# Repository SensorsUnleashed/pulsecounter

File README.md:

# Pulse Counter board

Simple mains powered board that will count any pulses applied to the connector.

RJ45 Connector Pin-out:
* RJ45 Pin 2 - VCC
* RJ45 Pin 5 - GND
* RJ45 Pin 6 - TTL Data

An example of a sensor that will fit the connector directly, can be found here: [Optical Utility Meter LED Pulse Sensor](https://openenergymonitor.org/emon/opticalpulsesensor)

Below you can see the prototype board.

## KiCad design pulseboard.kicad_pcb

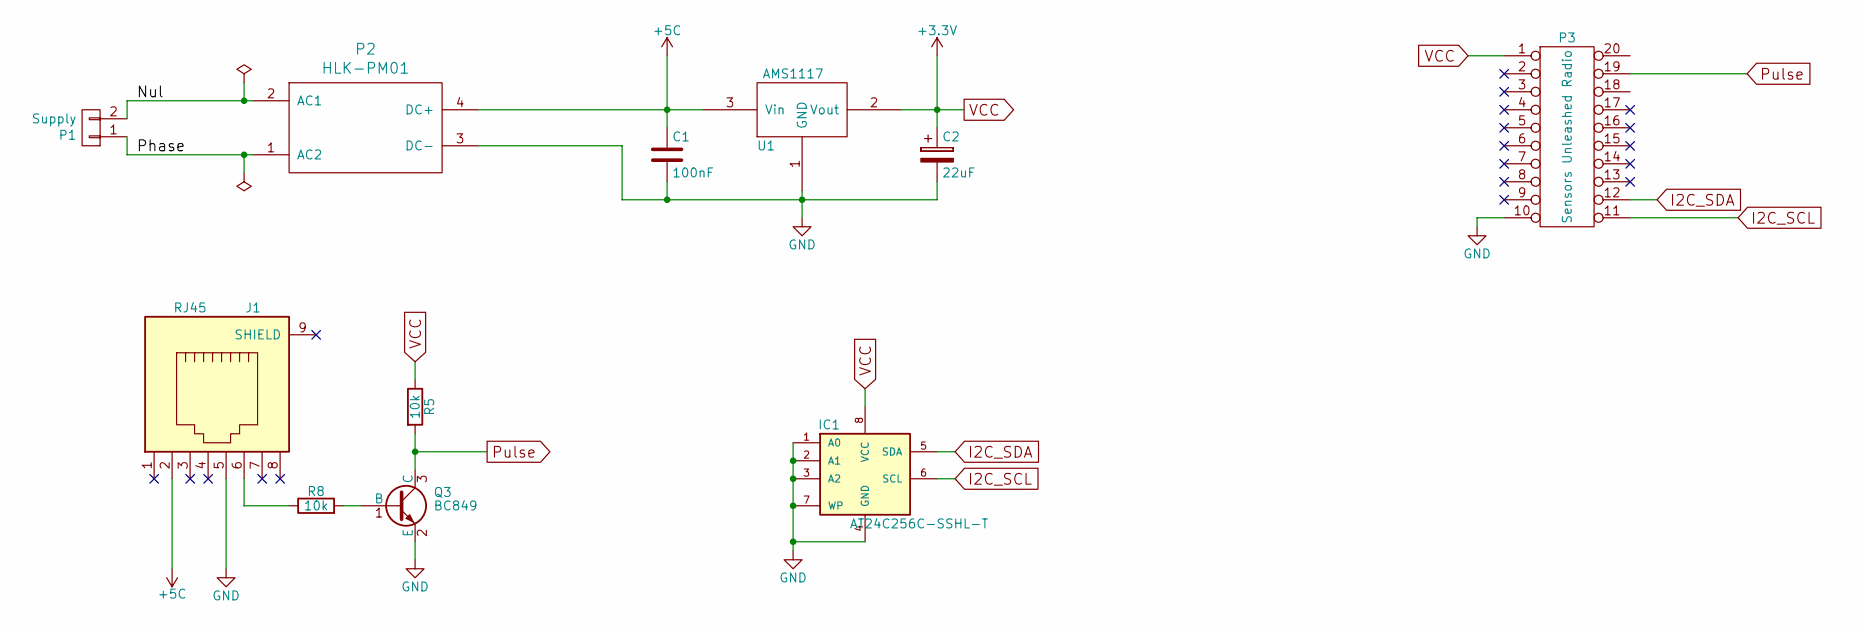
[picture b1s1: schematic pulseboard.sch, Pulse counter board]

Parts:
C1: 100nF; C_0805; Manufacturer Part Number 08053C104KAT2A
C2: 22uF; C_0805; Manufacturer Part Number F981A226MSA
IC1: AT24C256C-SSHL-T; SOIC-8_3.9x4.9mm_Pitch1.27mm
J1: RJ45; RJ45_8
P1: Supply; AK300-2
P2: HLK-PM01
P3: Sensors Unleashed Radio; zb3219PA_radio
Q3: BC849; SOT-23; Manufacturer Part Number BC849C-TP
R5, R8: 10k; R_0805
U1: AMS1117; SOT-223; Manufacturer Part Number AMS1117-3.3

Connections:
+5C: C1.1, J1.2, P2.4 (DC+), U1.3 (Vin)
/Nul: P1.2, P2.2 (AC1)
/Phase: P1.1, P2.1 (AC2)
GND: C1.2, C2.2, IC1.1 (A0), IC1.2 (A1), IC1.3 (A2), IC1.4 (GND), IC1.7 (WP), J1.5, P2.3 (DC-), P3.10, Q3.2 (E), U1.1 (GND)
I2C_SCL: IC1.6 (SCL), P3.11
I2C_SDA: IC1.5 (SDA), P3.12
unnamed: J1.6, R8.1
unnamed: Q3.1 (B), R8.2
Pulse: P3.19, Q3.3 (C), R5.2
VCC: C2.1, IC1.8 (VCC), P3.1, R5.1, U1.2 (Vout)

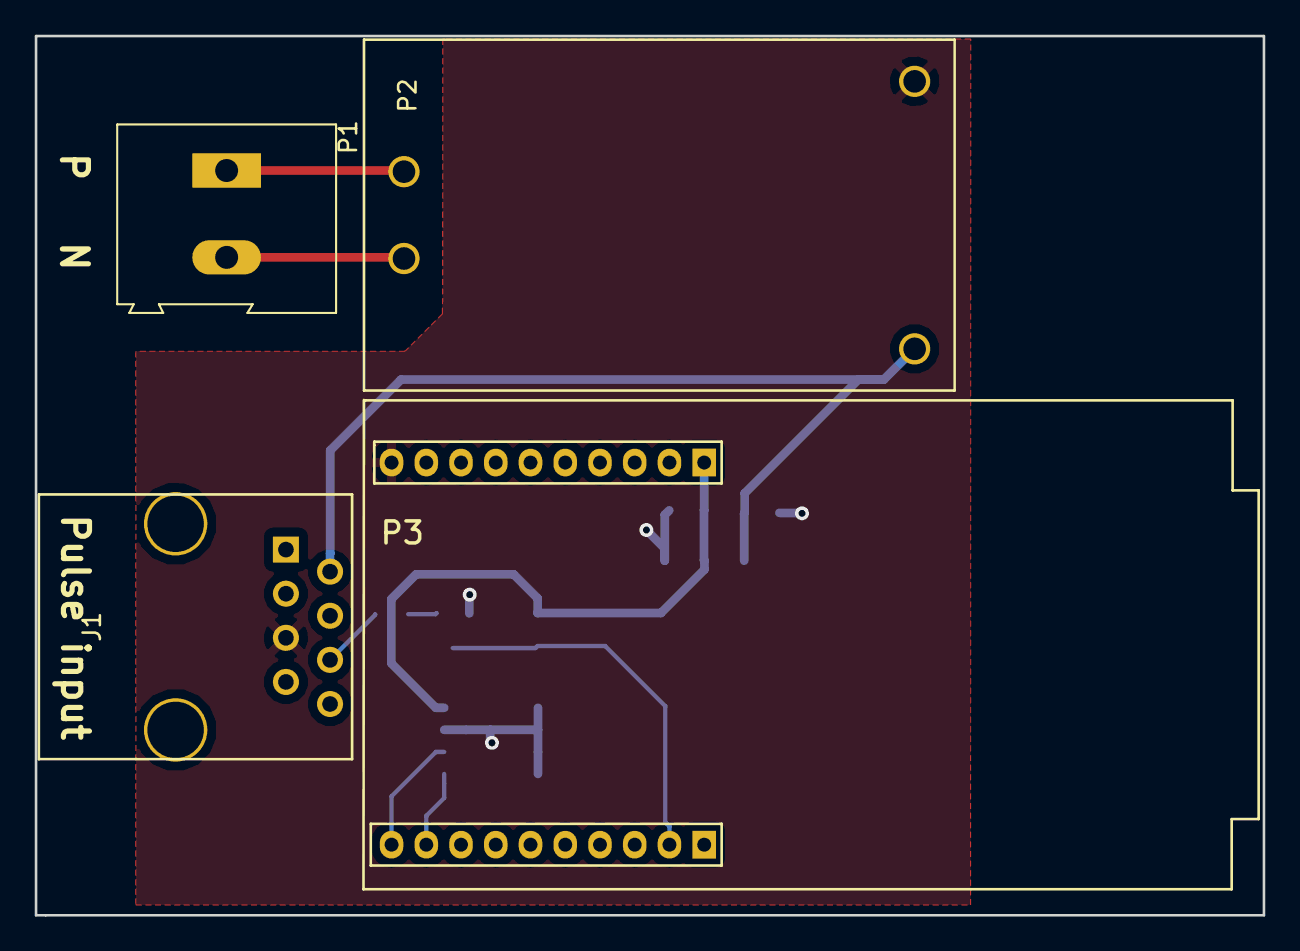
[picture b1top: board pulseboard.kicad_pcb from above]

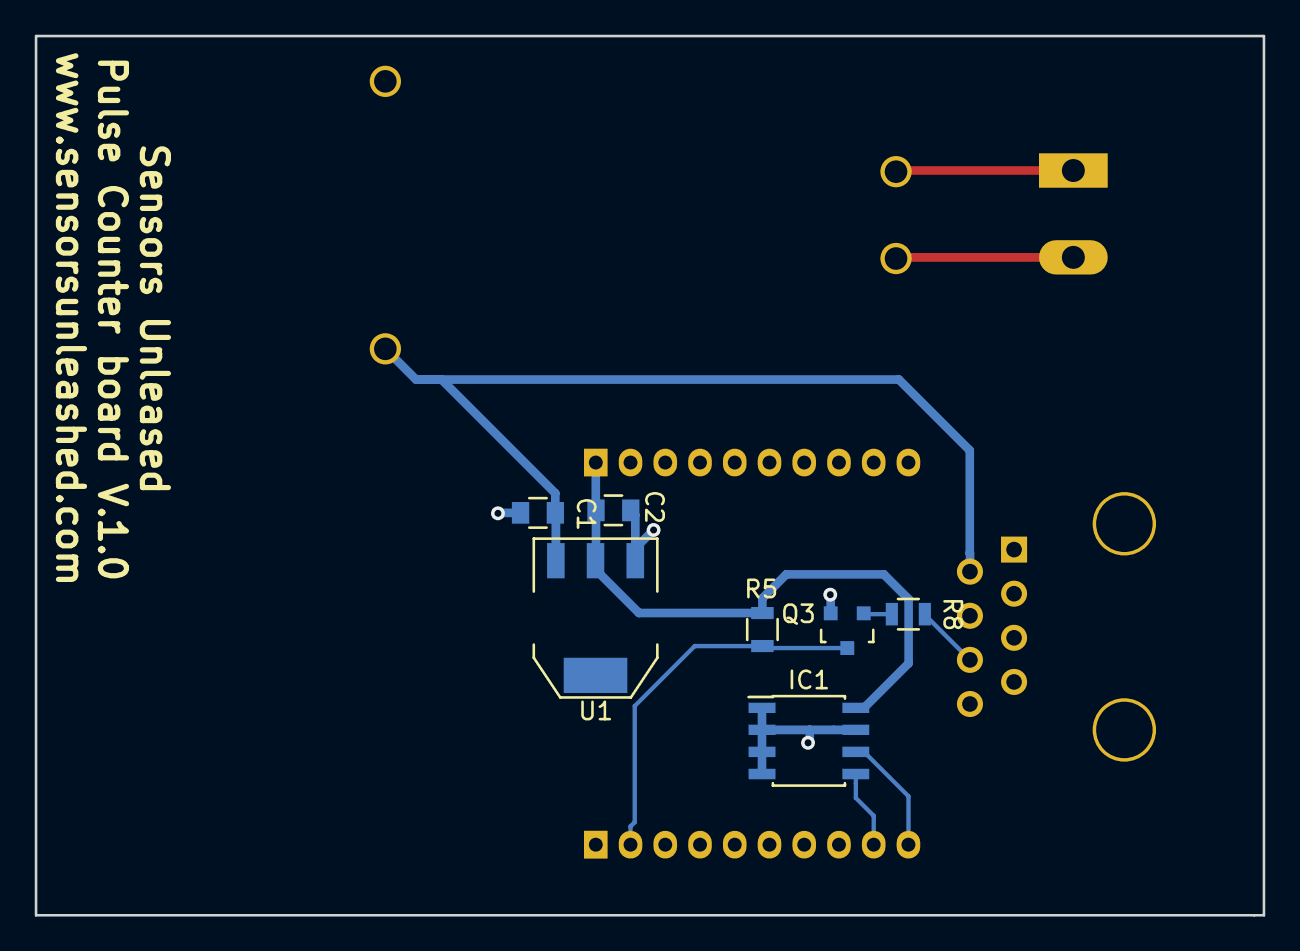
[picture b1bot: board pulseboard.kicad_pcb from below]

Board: 2 copper layers, 70.7 x 50.6 mm, 11 parts (7 on the bottom side), 10 nets.

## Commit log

2017-03-06 New release
2017-03-07 Resized the images to be webfriendly
